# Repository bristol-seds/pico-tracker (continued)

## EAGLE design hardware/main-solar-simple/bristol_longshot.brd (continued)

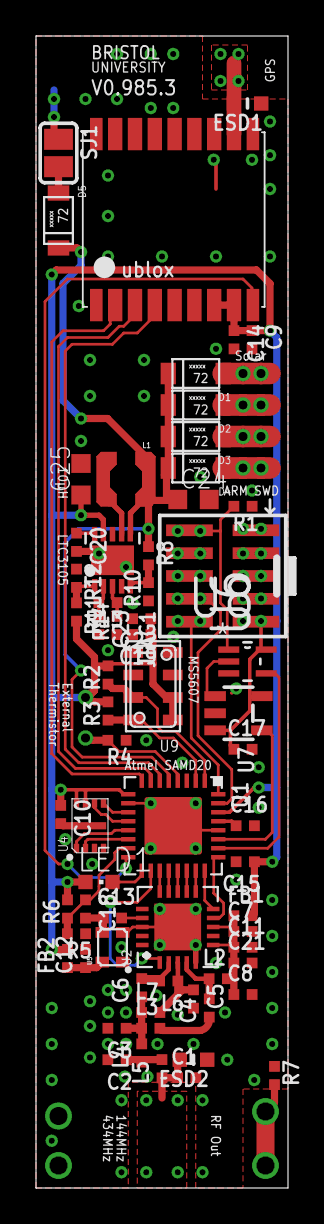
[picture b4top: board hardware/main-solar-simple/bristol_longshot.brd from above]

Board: 2 copper layers, 14.0 x 64.0 mm, 66 parts (0 on the bottom side), 50 nets.

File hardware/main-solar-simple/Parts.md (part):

# Parts List

** Parts for HF Section not yet included **

----
### Active

| Part | Description | Supplier | Quantity Required | Notes
| ---  | ---         | ---       | ---               | ---
|ATSAMD20E17A-MU|ATMEL - MCU, 32BIT, CORTEX-M0+, 48MHZ, QFN-32|[2361006](http://uk.farnell.com/webapp/wcs/stores/servlet/Search?st=2361006) [556-ATSAMD20E17A-MU](http://uk.mouser.com/Search/Refine.aspx?N=1323043&Keyword=55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|1|U1
|SI4468-A2A-IM|SILICON LABS - RF TRANSCEIVER, 0.142-1.05GHZ, HQFN-20|[2462639](http://uk.farnell.com/webapp/wcs/stores/servlet/Search?st=2462639) [634-SI4468-A2A-IM](http://uk.mouser.com/Search/Refine.aspx?N=1323043&Keyword=63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|1|U2
| UBLOX MAX-8C | GPS | [HAB Supplies](http://ava.upuaut.net/store/index.php?route=product/product&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 | 1 | U3
|SST25WF040BT-40I/NP|MICROCHIP - FLASH, 4MBIT, 40MHZ, USON-8|[2414758](http://uk.farnell.com/webapp/wcs/stores/servlet/Search?st=2414758) [579-25WF040BT-40I/NP](http://uk.mouser.com/Search/Refine.aspx?N=1323043&Keyword=57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|1|U4 memory 4Mbit
|X1G0041310008 TG-5006CJ-17H 16.369MHZ|EPSON - CRYSTAL, TCXO, TG-5006CJ-17H, 16.369 MHZ|[2405790](http://uk.farnell.com/webapp/wcs/stores/servlet/Search?st=2405790)|1|U5 TCXO Si4xxx
|LTC3105EDD#PBF|LINEAR TECHNOLOGY - BOOST, 400MA, MPPC, 10DFN|[1898600](http://uk.farnell.com/webapp/wcs/stores/servlet/Search?st=1898600)|1|U6 Solar Energy Boost Converter
|TPS3123J18DBVT|TEXAS INSTRUMENTS - IC, 1.62V SUPPLY MONITOR SOT-23-5|[1755607](http://uk.farnell.com/webapp/wcs/stores/servlet/Search?st=1755607) [595-TPS3123J18DBVT](http://uk.mouser.com/Search/Refine.aspx?N=1323043&Keyword=59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|1|U7 watchdog
|SN74LVC1G32DCKR|TEXAS INSTRUMENTS - IC, SINGLE 2 INPUT OR GATE, SMD|[1470880](http://uk.farnell.com/webapp/wcs/stores/servlet/Search?st=1470880) [595-SN74LVC1G32DCKR](http://uk.mouser.com/Search/Refine.aspx?N=1323043&Keyword=59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|1|U8 or-gate, watchdog subsystem
|MS560702BA03-50|MEASUREMENT SPECIALTIES - Pressure Sensor, QFN, 8, -40 Â°C, 85 Â°C, 1.8 V, 3.6 V|[2362660](http://uk.farnell.com/webapp/wcs/stores/servlet/Search?st=2362660)|1|U9 MS5607 Pressure / Temperature sensor
|RB161M-20TR|ROHM - Small Signal Schottky Diode, Single, 25 V, 1 A, 350 mV, 30 A, 125 Â°C|[1525484](http://uk.farnell.com/webapp/wcs/stores/servlet/Search?st=1525484)|5|D1, D2, D3, D4, D5 Small signal schotty diode
----

### Passives

| Part | Description | Supplier | Quantity Required | Notes
| ---  | ---         | ---       | ---               | ---
|LPS3015-103MRB|COILCRAFT - Surface Mount Power Inductor, AEC-Q200 LPS3015 Series, 10 ÂµH, Â± 20%, Shielded, 0.44 ohm, 550 mA|[2408024](http://uk.farnell.com/webapp/wcs/stores/servlet/Search?st=2408024)|1|L11 10µH LPS3015
|0402AF-221XJLU|COILCRAFT - Surface Mount High Frequency Inductor, 0402AF Series, 220 nH, Â± 5%, 0402 [1005 Metric], 1.15 GHz|[2285640](http://uk.farnell.com/webapp/wcs/stores/servlet/Search?st=2285640)|1|L2 220nH radio
|LQG15HN56NJ02D|MURATA - INDUCTOR, 0402 CASE, 56NHÂ±5%|[1343091](http://uk.farnell.com/webapp/wcs/stores/servlet/Search?st=1343091)|1|L3 56nH rf filter
|L-07C18NJV6T|JOHANSON TECHNOLOGY - Surface Mount High Frequency Inductor, L-07C Series, 18 nH, Â± 5%, 0402 [1005 Metric], 0.65 ohm|[1865775](http://uk.farnell.com/webapp/wcs/stores/servlet/Search?st=1865775)|1|L4, L5 18nH rf filter
| L6, L7 | DNP ||| si4xxx rx
|MC00625W0402110K|MULTICOMP - Surface Mount Chip Resistor, Thick Film, MC Series, 10 kohm, 62.5 mW, Â± 1%, 50 V|[1358069](http://uk.farnell.com/webapp/wcs/stores/servlet/Search?st=1358069)|7|R1, R2, R3 10k
|ERA2AED104X|PANASONIC ELECTRONIC COMPONENTS - Surface Mount Chip Resistor, Metal Film, AEC-Q200 ERA Series, 100 kohm, 63 mW, Â± 0.5%, 25 V|[2324718](http://uk.farnell.com/webapp/wcs/stores/servlet/Search?st=2324718)|1|R4 100k precise
|CRG0402F100K|TE CONNECTIVITY - Surface Mount Chip Resistor, Thick Film, CRG Series, 100 kohm, 63 mW, Â± 1%, 50 V|[2331442](http://uk.farnell.com/webapp/wcs/stores/servlet/Search?st=2331442)|2|R5, R6 100k
|RC0402JR-070RL|YAGEO (PHYCOMP) - Surface Mount Chip Resistor, Thick Film, RC Series, 0 ohm, 62.5 mW, Â± 5%, 50 V, 0402 [1005 Metric]|[9232516](http://uk.farnell.com/webapp/wcs/stores/servlet/Search?st=9232516)|1|R7 Bridge 0Ω
| R8 | DNP ||| connect MPPT set when battery only is used
|CRG0402F82K|TE CONNECTIVITY - Surface Mount Chip Resistor, Thick Film, CRG Series, 82 kohm, 63 mW, Â± 1%, 50 V, 0402 [1005 Metric]|[2331569](http://uk.farnell.com/webapp/wcs/stores/servlet/Search?st=2331569)|3|R10, R12, R14 LTC3105 82k
|CRG0402F68K|TE CONNECTIVITY - Surface Mount Chip Resistor, Thick Film, CRG Series, 68 kohm, 63 mW, Â± 1%, 50 V, 0402 [1005 Metric]|[2331557](http://uk.farnell.com/webapp/wcs/stores/servlet/Search?st=2331557)|1|R11 LTC3105 FB 68k
|MC00625W0402156K|MULTICOMP - Surface Mount Chip Resistor, Thick Film, MC Series, 56 kohm, 62.5 mW, Â± 1%, 50 V|[1358089](http://uk.farnell.com/webapp/wcs/stores/servlet/Search?st=1358089)|1|R13 LTC3105 LDOFB 56k
|GRM1555C1H8R2CA01D|MURATA - SMD Multilayer Ceramic Capacitor, GRM Series, 8.2 pF, Â± 0.25pF, C0G / NP0, 50 V, 0402 [1005 Metric]|[1828874](http://uk.farnell.com/webapp/wcs/stores/servlet/Search?st=1828874)|2|C1, C3 8.2pF
|MC0402N150J500CT|MULTICOMP - SMD Multilayer Ceramic Capacitor, MC Series, 15 pF, Â± 5%, C0G / NP0, 50 V, 0402 [1005 Metric]|[1758945](http://uk.farnell.com/webapp/wcs/stores/servlet/Search?st=1758945)|3|C2, C4, C7 15pF
| C5, C6 | DNP ||| si4xxx rx
|MC0402N101J500CT|MULTICOMP - SMD Multilayer Ceramic Capacitor, MC Series, 100 pF, Â± 5%, C0G / NP0, 50 V, 0402 [1005 Metric]|[1758969](http://uk.farnell.com/webapp/wcs/stores/servlet/Search?st=1758969)|3|C8, C9, C10 100pF
|MC0402X104K100CT|MULTICOMP - SMD Multilayer Ceramic Capacitor, MC Series, 0.1 ÂµF, Â± 10%, X5R, 10 V, 0402 [1005 Metric]|[1759380](http://uk.farnell.com/webapp/wcs/stores/servlet/Search?st=1759380)|9|C11, C12, C13, C14, C15, C16, C17, C18, C19 100nF
|GRM155R61E105KA12D|MURATA - SMD Multilayer Ceramic Capacitor, GRM Series, 1 ÂµF, Â± 10%, X5R, 25 V, 0402 [1005 Metric]|[2218855](http://uk.farnell.com/webapp/wcs/stores/servlet/Search?st=2218855)|1|C20 LTC3015 AUX 1µF
|GRM155R60J225ME15D|MURATA - SMD Multilayer Ceramic Capacitor, GRM Series, 2.2 ÂµF, Â± 20%, X5R, 6.3 V, 0402 [1005 Metric]|[2362088](http://uk.farnell.com/webapp/wcs/stores/servlet/Search?st=2362088)|1|C21 Radio Bypass 2.2µF
|C1005X5R0J475M050BC|TDK - SMD Multilayer Ceramic Capacitor, C Series, 4.7 ÂµF, Â± 20%, X5R, 6.3 V, 0402 [1005 Metric]|[2309027](http://uk.farnell.com/webapp/wcs/stores/servlet/Search?st=2309027)|2|C22, C23 MS5607 Bypass, LTC3105 LDO 4.7µF
|06036D106MAT2A|AVX - SMD Multilayer Ceramic Capacitor, 10 ÂµF, Â± 20%, X5R, 6.3 V, 0603 [1608 Metric]|[1833804](http://uk.farnell.com/webapp/wcs/stores/servlet/Search?st=1833804)|2|C24, C25 LTC3105 in, out 10µF 0603

----

### Misc

| Part | Description | Supplier | Quantity Required | Notes
| ---  | ---         | ---       | ---               | ---
|20021121-00010C4LF.|FCI - Board-To-Board Connector, Minitek127 20021121 Series, Surface Mount, Header, 10, 1.27 mm|[1865279](http://uk.farnell.com/webapp/wcs/stores/servlet/Search?st=1865279) [649-202112100010C4LF](http://uk.mouser.com/Search/Refine.aspx?N=1323043&Keyword=64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|1|JTAG1
|742792731|WURTH ELEKTRONIK - FERRITE BEAD, 0.09OHM, 1.2A, 0402|[1961698](http://uk.farnell.com/webapp/wcs/stores/servlet/Search?st=1961698)|2|FB1, FB2
|CG0603MLC-05LE|BOURNS - ESD Protection Device, 25 V, 5 V, 0603, 2|[1828732](http://uk.farnell.com/webapp/wcs/stores/servlet/Search?st=1828732)|0|ESD1, ESD2
|B57861S0103F040|EPCOS - THERMISTOR, 10K, 1%, NTC, RAD|[679446](http://uk.farnell.com/webapp/wcs/stores/servlet/Search?st=679446)|1|External Thermistor
| | Antenna Wire | [ebay](http://www.ebay.co.uk/itm/Ernie-Ball-Custom-Gauge-Guitar-Sin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 ) | 1 | Ernie Ball .013
| | Energizer Ultimate Lithium AAA | [datasheet](http://data.energizer.com/PDFs/l92.pdf) | 1 | ~1200mAh

----

## AAA Hardware

| ID | Part Number | Description | Supplier | Order Code | Quantity
| --- | --- | --- | --- | --- | ---
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
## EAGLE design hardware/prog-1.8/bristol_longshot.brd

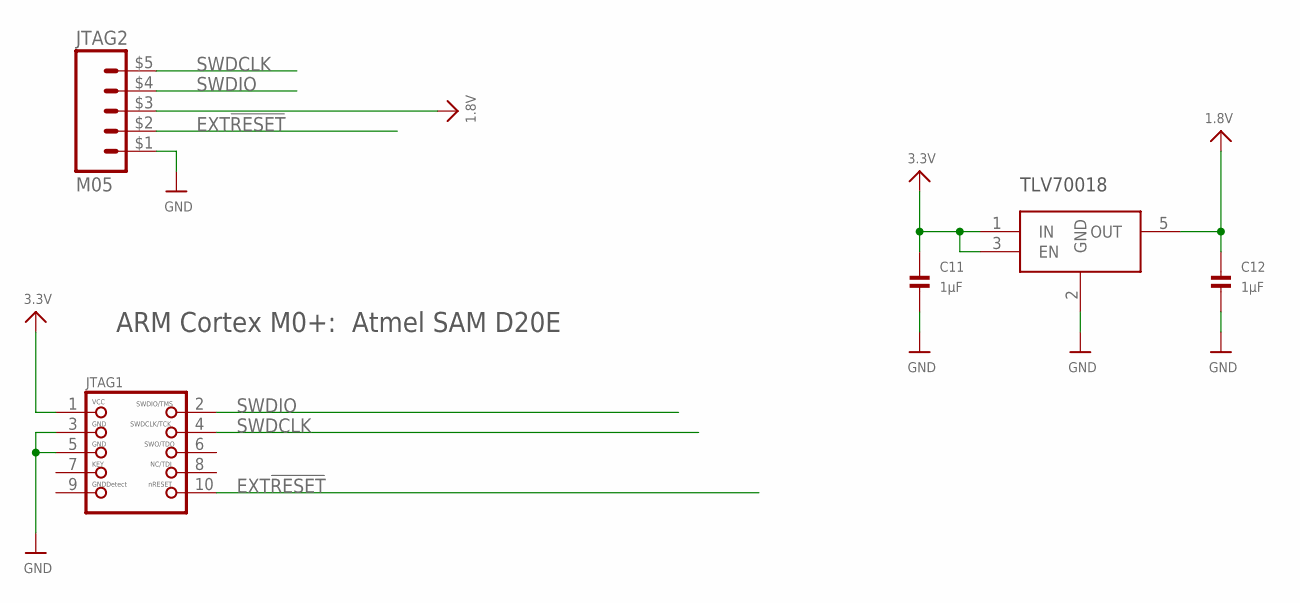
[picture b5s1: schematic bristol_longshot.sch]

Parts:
C11, C12: 1µF; _0402
JTAG1: JTAG-CORTEXM3SMT; 2X05_1.27MM_SMT
JTAG2: M05; M05_SIDE
U1: TLV70018DCK; SC70-5L

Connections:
1.8V: C12.1, JTAG2.$3 (3), U1.5 (OUT)
3.3V: C11.1, JTAG1.1, U1.1 (IN), U1.3 (EN)
EXT!RESET: JTAG1.10, JTAG2.$2 (2)
GND: C11.2, C12.2, JTAG1.3, JTAG1.5, JTAG2.$1 (1), U1.2 (GND)
SWDCLK: JTAG1.4, JTAG2.$5 (5)
SWDIO: JTAG1.2, JTAG2.$4 (4)

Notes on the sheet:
ARM Cortex M0+: Atmel SAM D20E
TLV70018

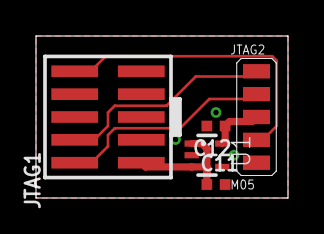
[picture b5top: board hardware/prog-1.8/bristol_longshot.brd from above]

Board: 2 copper layers, 14.0 x 9.0 mm, 5 parts (0 on the bottom side), 6 nets.

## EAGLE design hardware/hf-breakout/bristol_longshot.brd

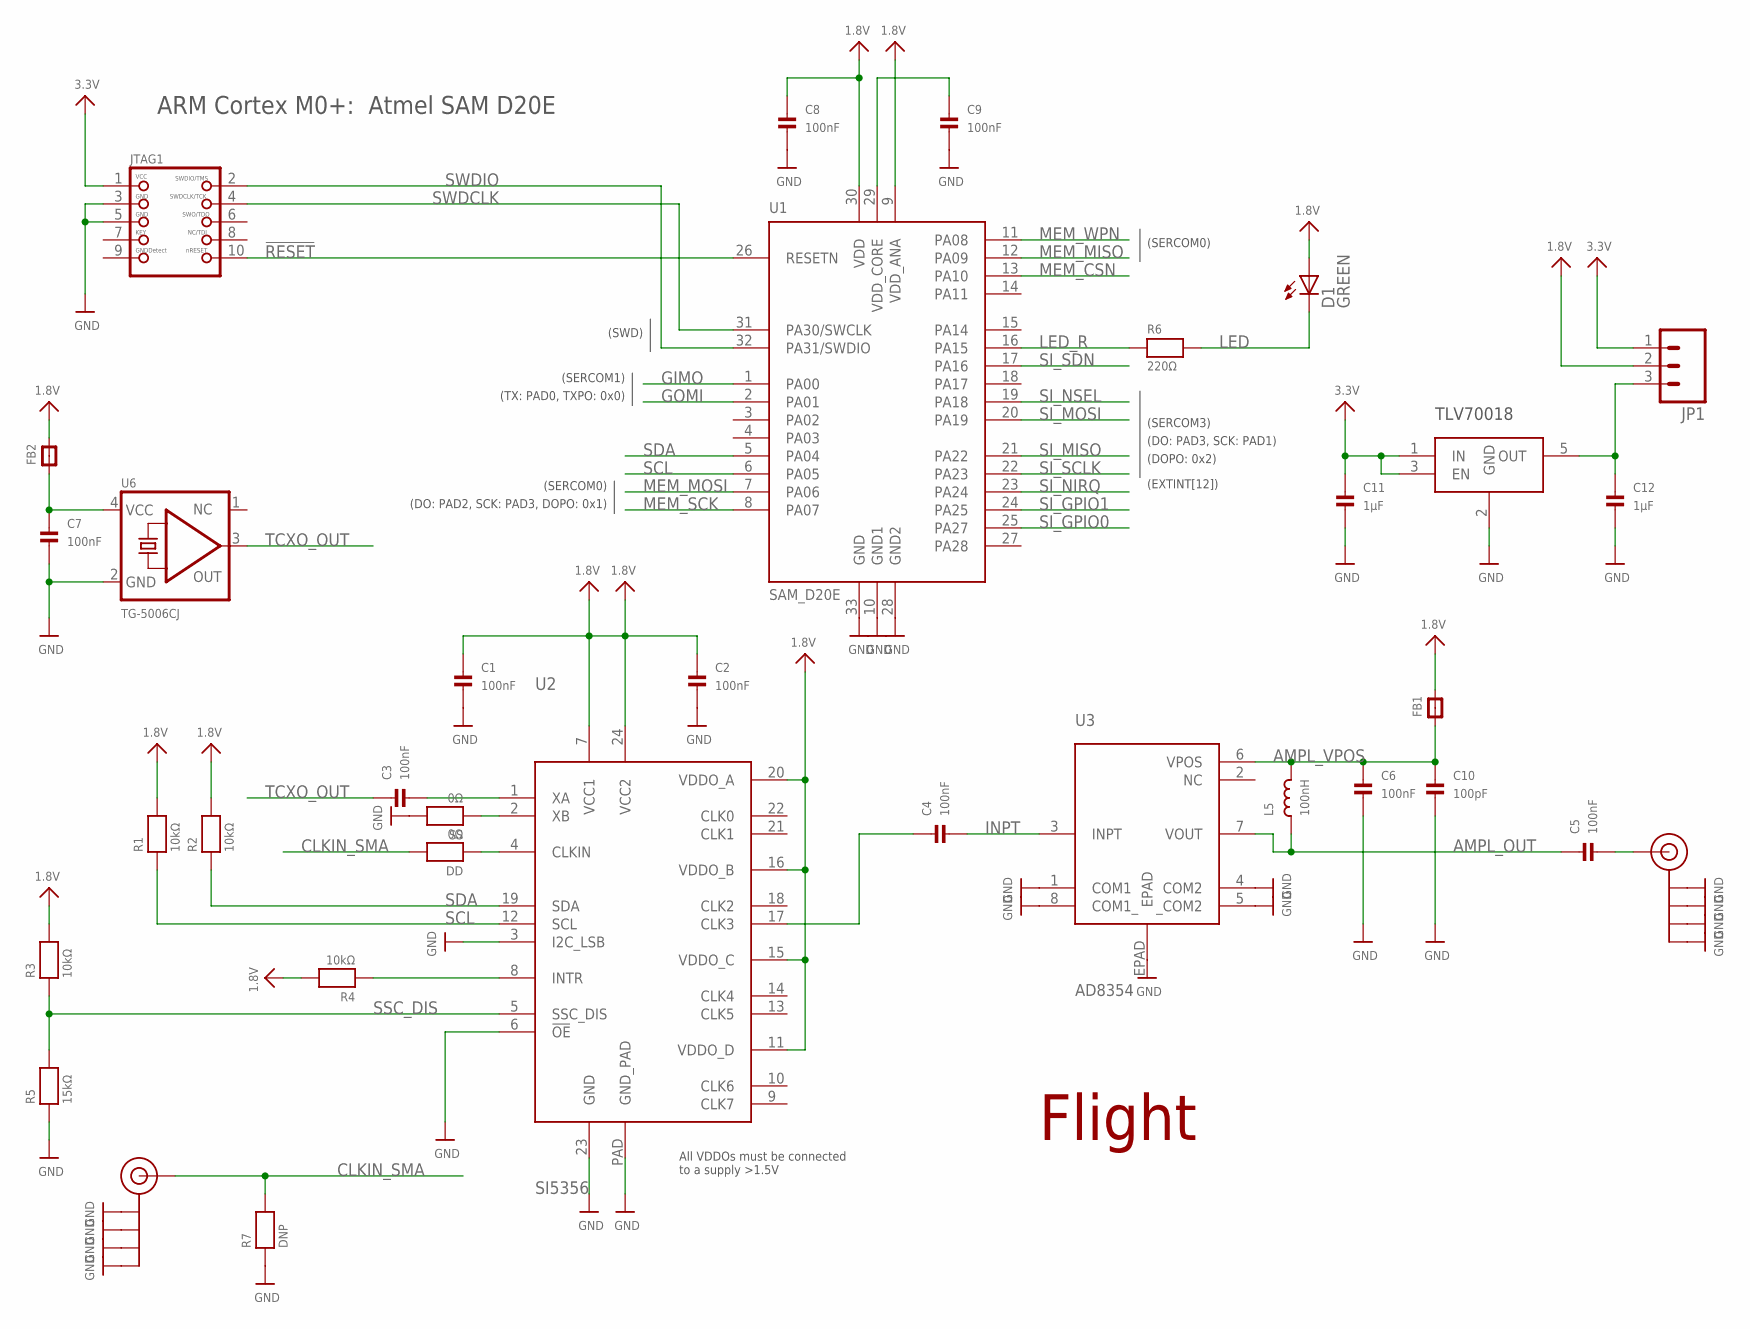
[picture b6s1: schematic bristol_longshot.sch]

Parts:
C1, C2, C3, C4, C5, C6, C7, C8, C9: 100nF; _0402
C10: 100pF; _0402
C11, C12: 1µF; _0402
D1: GREEN; CHIPLED_0603
DD: 0Ω; _0402
FB1, FB2: FERRITE_0402; _0402
IC3: TLV70018DCK; SC70-5L
J$1, J$2: SMA_EDGE; SMA-EDGE
JP1: M03LOCK; 1X03_LOCK
JTAG1: JTAG-CORTEXM3SMT; 2X05_1.27MM_SMT
L5: 100nH; _0402
R1, R2, R3, R4: 10kΩ; _0402
R5: 15kΩ; _0402
R6: 220Ω; _0402
R7: DNP; _0402
SS: 0Ω; _0402
U1: SAM_D20E; QFN32_5MM
U2: SI5356; QFN24_4MM
U3: AD8354; LFCSP_VD_8
U6: TG-5006CJ; TC-5006CJ

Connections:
1.8V: C1.1, C2.1, C8.1, D1.A, FB1.2, FB2.2, JP1.2, R1.2, R2.2, R3.2, R4.2, U1.9 (VDD_ANA), U1.30 (VDD), U2.7 (VCC1), U2.11 (VDDO_D), U2.15 (VDDO_C), U2.16 (VDDO_B), U2.20 (VDDO_A), U2.24 (VCC2)
3.3V: C11.1, IC3.1 (IN), IC3.3 (EN), JP1.1, JTAG1.1; also elsewhere on the board
!RESET: JTAG1.10, U1.26 (RESETN)
AMPL_OUT: C5.1, L5.1, U3.7 (VOUT)
AMPL_VPOS: C6.1, C10.1, FB1.1, L5.2, U3.6 (VPOS)
CLKIN: DD.1, U2.4 (CLKIN)
CLKIN_SMA: DD.2, J$1.SIG (SIGNAL), R7.2
GIMO: U1.1 (PA00)
GND: C1.2, C2.2, C6.2, C7.2, C8.2, C9.2, C10.2, C11.2, C12.2, IC3.2 (GND), J$1.GND@0 (GND), J$1.GND@1 (GND), J$1.GND@2 (GND), J$1.GND@3 (GND), J$2.GND@0 (GND), J$2.GND@1 (GND), J$2.GND@2 (GND), J$2.GND@3 (GND), JTAG1.3, JTAG1.5, R5.1, R7.1, SS.2, U1.10 (GND1), U1.28 (GND2), U1.33 (GND), U2.3 (I2C_LSB), U2.6 (!OE), U2.23 (GND), U2.PAD (GND_PAD), U3.1 (COM1), U3.4 (COM2), U3.5 (_COM2), U3.8 (COM1_), U3.EPAD, U6.2 (GND); also elsewhere on the board
GOMI: U1.2 (PA01)
HF: C5.2, J$2.SIG (SIGNAL)
HF_CLK: C4.1, U2.17 (CLK3)
INPT: C4.2, U3.3 (INPT)
INTR: R4.1, U2.8 (INTR)
LED: D1.C, R6.2
LED_R: R6.1, U1.16 (PA15)
MEM_CSN: U1.13 (PA10)
MEM_MISO: U1.12 (PA09)
MEM_MOSI: U1.7 (PA06)
MEM_SCK: U1.8 (PA07)
MEM_WPN: U1.11 (PA08)
unnamed 22: C12.1, IC3.5 (OUT), JP1.3; also elsewhere on the board
SCL: R1.1, U1.6 (PA05), U2.12 (SCL)
SDA: R2.1, U1.5 (PA04), U2.19 (SDA)
SI_GPIO0: U1.25 (PA27)
SI_GPIO1: U1.24 (PA25)
SI_MISO: U1.21 (PA22)
SI_MOSI: U1.20 (PA19)
SI_NIRQ: U1.23 (PA24)
SI_NSEL: U1.19 (PA18)
SI_SCLK: U1.22 (PA23)
SI_SDN: U1.17 (PA16)
SSC_DIS: R3.1, R5.2, U2.5 (SSC_DIS)
SWDCLK: JTAG1.4, U1.31 (PA30/SWCLK)
SWDIO: JTAG1.2, U1.32 (PA31/SWDIO)
TCXO_OUT: C3.1, U6.3 (OUT)
TCXO_VDD: C7.1, FB2.1, U6.4 (VCC)
VDD_CORE: C9.1, U1.29 (VDD_CORE)
XA: C3.2, U2.1 (XA)
XB: SS.1, U2.2 (XB)

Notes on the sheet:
ARM Cortex M0+: Atmel SAM D20E
(SERCOM3)
(SWD)
(SERCOM0)
(EXTINT[12])
(DO: PAD3, SCK: PAD1)
(DOPO: 0x2)
(DO: PAD2, SCK: PAD3, DOPO: 0x1)
(SERCOM1)
(TX: PAD0, TXPO: 0x0)
Flight
All VDDOs must be connected to a supply >1.5V
TLV70018

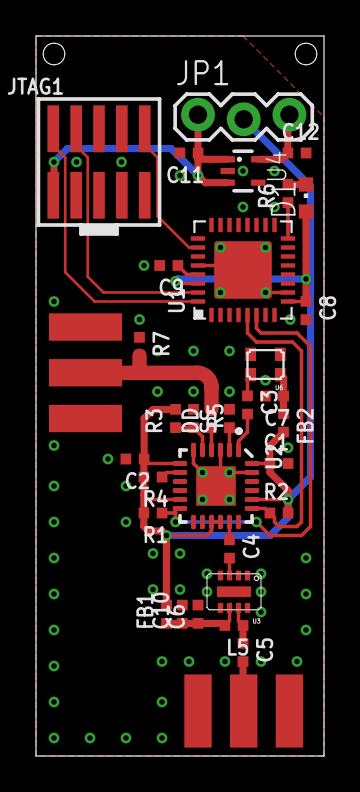
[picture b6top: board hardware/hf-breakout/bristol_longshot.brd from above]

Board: 2 copper layers, 16.0 x 40.0 mm, 34 parts (0 on the bottom side), 25 nets.

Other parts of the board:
U4: TLV70018DCK; SC70-5L

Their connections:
3.3V: U4.1, U4.3; also elsewhere on the board
GND: U4.2; also elsewhere on the board
unnamed 22: U4.5; also elsewhere on the board

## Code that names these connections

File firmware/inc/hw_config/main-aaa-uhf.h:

/*
 * Hardware definitions and configuations
 * Copyright (C) 2014  Richard Meadows <richardeoin>
 *
 * Permission is hereby granted, free of charge, to any person obtaining
 * a copy of this software and associated documentation files (the
 * "Software"), to deal in the Software without restriction, including
 * without limitation the rights to use, copy, modify, merge, publish,
 * distribute, sublicense, and/or sell copies of the Software, and to
 * permit persons to whom the Software is furnished to do so, subject to
 * the following conditions:
 *
 * The above copyright notice and this permission notice shall be
 * included in all copies or substantial portions of the Software.
 *
 * THE SOFTWARE IS PROVIDED "AS IS", WITHOUT WARRANTY OF ANY KIND,
 * EXPRESS OR IMPLIED, INCLUDING BUT NOT LIMITED TO THE WARRANTIES OF
 * MERCHANTABILITY, FITNESS FOR A PARTICULAR PURPOSE AND
 * NONINFRINGEMENT. IN NO EVENT SHALL THE AUTHORS OR COPYRIGHT HOLDERS BE
 * LIABLE FOR ANY CLAIM, DAMAGES OR OTHER LIABILITY, WHETHER IN AN ACTION
 * OF CONTRACT, TORT OR OTHERWISE, ARISING FROM, OUT OF OR IN CONNECTION
 * WITH THE SOFTWARE OR THE USE OR OTHER DEALINGS IN THE SOFTWARE.
 */

#ifndef HW_CONFIG_H
#define HW_CONFIG_H

#include "port.h"
#include "samd20.h"
#include "adc/adc.h"

/*
 * Convenience definitions for available GPIO modules
 */
#if (PORT_GROUPS > 0)
#define PORTA		PORT->Group[0]
#endif
#if (PORT_GROUPS > 1)
#define PORTB		PORT->Group[1]
#endif
#if (PORT_GROUPS > 2)
#define PORTC		PORT->Group[2]
#endif
#if (PORT_GROUPS > 3)
#define PORTD		PORT->Group[3]
#endif


//#define XPLAINED

/**
 * LED
 */
#ifdef XPLAINED
#define LED0_PIN		PIN_PA14
#else
#define LED0_PIN		PIN_PA16
#endif

/**
 * GPS
 */
#define GPS_SERCOM		(SercomUsart*)SERCOM0
#define GPS_SERCOM_MOGI_PIN	PIN_PA06
#define GPS_SERCOM_MOGI_PINMUX	PINMUX_PA06D_SERCOM0_PAD2
#define GPS_SERCOM_MIGO_PIN	PIN_PA07
#define GPS_SERCOM_MIGO_PINMUX	PINMUX_PA07D_SERCOM0_PAD3
#define GPS_SERCOM_MUX		USART_RX_3_TX_2_XCK_3
#define GPS_GCLK		GCLK_GENERATOR_1

#define GPS_TYPE_UBX
#define GPS_BAUD_RATE		9600
#define GPS_PLATFORM_MODEL	UBX_PLATFORM_MODEL_AIRBORNE_1G
#define GPS_TIMEPULSE_PIN	PIN_PA05
#define GPS_TIMEPULSE_PINMUX	PINMUX_PA05A_EIC_EXTINT5
#define GPS_TIMEPULSE_FREQ      1
#define GPS_TIMEPULSE_EXTINT	5
#define GPS_RESET_PIN		PIN_PA15

#define GPS_FLIGHT_STATE_THREASHOLD_M	8000 /* 8km altitude */

/**
 * USART Loopback Testing
 */
#define USART_MUX_LOOPBACK	USART_RX_2_TX_2_XCK_3


/**
 * Battery ADC
 */
#define BATTERY_ADC			1
#define BATTERY_ADC_PIN		PIN_PA03
#define BATTERY_ADC_PINMUX	PINMUX_PA03B_ADC_AIN1
#define BATTERY_ADC_CHANNEL	ADC_POSITIVE_INPUT_PIN1
#define BATTERY_ADC_CHANNEL_DIV	0.3125 /* ??? */
#define BATTERY_ADC_REFERENCE	ADC_REFERENCE_INT1V

/**
 * External Thermistor ADC
 */
#define THERMISTOR_ADC		0
#define THERMISTOR_ADC_PIN	PIN_PA03
#define THERMISTOR_ADC_PINMUX	PINMUX_PA03
#define THERMISTOR_ADC_CHANNEL	ADC_POSITIVE_INPUT_PIN1
#define THERMISTOR_ADC_CHANNEL_DIV 1
#define THERMISTOR_ADC_REFERENCE ADC_REFERENCE_INTVCC0 /* internal 1/1.48 VCC reference */

/**
 * Solar ADC
 */
#define SOLAR_ADC			0
#define SOLAR_ADC_PIN		PIN_PA04
#define SOLAR_ADC_PINMUX	PINMUX_PA04B_ADC_AIN4
#define SOLAR_ADC_CHANNEL	ADC_POSITIVE_INPUT_PIN4
#define SOLAR_ADC_CHANNEL_DIV	1
#define SOLAR_ADC_REFERENCE	ADC_REFERENCE_INT1V

/**
 * Battery
 */
#define RECHARGABLE_BATTERY	0

/**
 * Cycle Times
 */
#define CYCLE_TIME_FAST		(30)   /* always 30 seconds */
#define CYCLE_TIME_SLOW		(30)

/**
 * Radio
 */
#define SI4xxx_RADIO_PN		0x4467
#define SI4xxx_SERCOM		(SercomSpi*)SERCOM3
#define SI4xxx_SERCOM_MOSI_PIN	PIN_PA19
#define SI4xxx_SERCOM_MOSI_PINMUX PINMUX_PA19D_SERCOM3_PAD3
#define SI4xxx_SERCOM_MISO_PIN	PIN_PA22
#define SI4xxx_SERCOM_MISO_PINMUX PINMUX_PA22C_SERCOM3_PAD0
#define SI4xxx_SERCOM_SCK_PIN	PIN_PA23
#define SI4xxx_SERCOM_SCK_PINMUX	PINMUX_PA23C_SERCOM3_PAD1
#define SI4xxx_SERCOM_MUX	SPI_SIGNAL_MUX_SETTING_M
#define SI4xxx_SEL_PIN		PIN_PA18
#define SI4xxx_IRQ_PIN		PIN_PA24
#define SI4xxx_IRQ_PINMUX	PINMUX_PA24A_EIC_EXTINT12
#define SI4xxx_SDN_PIN		PIN_PA17
#define SI4xxx_GPIO0_PIN	PIN_PA27
#define SI4xxx_GPIO1_PIN	PIN_PA25
#define SI4xxx_GPIO1_PINMUX	PINMUX_PA25F_TC5_WO1
#define SI4xxx_TCXO_FREQUENCY	16369000

/**
 * RF Power @ 1.8V
 *
 * These values are taken from the datasheet, but the
 * difference between them has been measured as 6dB
 */
#define RF_POWER_14dBm		0x7f
#define RF_POWER_8dBm		0x7f /* tested in lab (36) */


/**
 * RF Enable
 *
 * Disable this when there's no antenna connected
 */
#define RF_TX_ENABLE		1

/**
 * LF Clock
 */
#define USE_LFTIMER			0

/**
 * XOSC
 */
#define USE_XOSC				1
#define XOSC_FREQUENCY			16369000
#define XOSC_GCLK_DIVIDE		2         /* ~8MHz on GCLK */
#define OSC8M_GCLK_DIVIDE		1         /* ~8MHz on GCLK */
#define MEASURE_XOSC			1

/**
 * Telemetry
 */
#define TELEMETRY_ENABLE		1
#define TELEMETRY_USE_GEOFENCE	0
#define TELEMETRY_FREQUENCY		434612500
#define TELEMETRY_POWER			RF_POWER_8dBm

/**
 * APRS
 */
#define APRS_ENABLE			0
#define APRS_USE_GEOFENCE	0
#define APRS_POWER			RF_POWER_14dBm

/**
 * Backlog
 */
#define BACKLOG_RECORD_BACKLOG	0

/**
 * Watchdog Timer
 *
 * There is a performance penalty to using the watchdog - you must
 * wait up to 1/16kHz when kicking to sync with it. Disable when not in use
 */
//#define DEBUG_USE_INTWATCHDOG	0
#define WDT_GCLK		GCLK_GENERATOR_4

/**
 * External Watchdog Timer
 */
#define WDT_WDI_PIN		PIN_PA28

/**
 * SWD
 */
#define SWD_SWDCLK_PIN		PIN_PA30
#define SWD_SWDCLK_PINMUX	PINMUX_PA30G_CORE_SWCLK
#define SWD_SWDIO_PIN		PIN_PA31


/**
 * Interrupt Priority
 */
#define WDT_INT_PRIO		0 /* Early warning interrupt */

#define TC0_INT_PRIO		1 /* Telemetry Tick Timer */

#define GPS_SERCOM_INT_PRIO	2 /* GPS USART Rx */

#define EIC_INT_PRIO		3 /* Timepulse, telemetry */

#define TC2_INT_PRIO		3 /* XOSC Measure Timer */

#define TC4_INT_PRIO		3 /* LF timer */
#define RTC_INT_PRIO		3 /* RTC */

#define ADC_INT_PRIO		3 /* ADC */

#endif /* HW_CONFIG_H */

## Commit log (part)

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2015-07-24 Timeout and retries on gps position and time. Lock and wait for hardware reset after 5 tries
2015-07-24 [Ooops] Fix logical error from eaa6469
2015-07-24 Enabled aprs parameters for flight
2015-07-25 Invalidate bad backlog items as they're read from memory
2015-07-25 Link to parts list for ubseds6 tag
2015-07-25 UBSEDS9 pre-flight
2015-08-01 raw_parser: Prompt if filename not specified
2015-08-01 Added habitat upload. Not complete yet but close #6
2015-08-02 Habitat upload done. 'time_created' corresponds to the backlog time, gets sorted correctly by the habitat couchdb views
2015-08-02 Added barometeric altitude model and testcase
2015-09-13 Updated main tracker solar design to use a LTC3105 energy harvester for solar and a 3V primary lithium for backup. Work in Progress
2015-09-15 Updated schematic labels, fixed R11 value
2015-09-15 Added README describing hardware revisions
2015-09-21 Hardware V0.985.2, replaces BMP180 with MS5607
2015-09-22 Small board change..
2015-10-01 Added module and tests for BMP180
2015-10-01 Add option for TELEMETRY_USE_GEOFENCE, disable APRS
2015-10-06 Tidy various compiler warnings
2015-10-06 Save some flash
2015-10-06 Enable aprs, telemetry geofence for testing
2015-10-06 Add thermistor voltage readings to analogue.c
    analogue.c is now configured from hw_config.h. Refactored a few things including the testcase.
2015-10-06 Added data field to UKHAS string
2015-10-08 Hardware v0.985.3, reduce external thermistor holes to 0.5mm dia
2015-10-08 Fix GPS reset
2015-10-08 Change data collection to once per minute, aligned with the Telemetry top-of-minute.
    Also some more rigourous accounting of the ukhas telemetry size
2015-10-09 Add BMP180 to data.c, format output correctly
2015-10-09 Finish removing semihost stuff
2015-10-10 Memory JEDEC ID in variable for debugging
2015-10-10 Increase ADC sample length, use internal ADC averaging.
2015-10-11 UBSEDS10
2015-10-18 Added UBX CFG PWR frame to GPS. Useful for putting GPS in "shutdown"
2015-10-28 Added hardware note for UBSEDS10-11
2015-10-28 [low-power-side] More work on board, vaguely complete. Added parts list
2015-11-02 Re-organised for two barometers
2015-11-02 [low-power-side] Added 10k i2c pull ups
    v0.986.0 -> v0.986.1
2015-11-10 low-power-side v0.986.4. Added LIS2D accelerometer. Optional
2015-11-14 [geofence] Restructure geofence notebooks, split aprs into frequency zone and no_aprs areas
    location.c need to be refactored to reflect these changes
2015-11-16 [gps] Started support for SiRF IV gps units in gps_osp.c. Split this away from gps_ubx.c
    TODO: Integrate osp gps support into cron.c, data.c etc.
2015-11-17 [low-power-side] v0.986.5 Added TS3006 low power clock
2015-11-20 [bugfix] Always 8-bit write corrected generator ID before reading
2015-11-22 [low power] v0.986.7. Changed low power lf clock, added vreg on breakout for optional power testing
2015-11-22 Commit thermistor.c, should have been added in f35ccb540b734aa2510d3fa96e54fe8df9596a13
2015-11-22 Rename geofence_aprs to geofence_aprs_zones for clarity
2015-11-22 [bugfix] re-order lat and lon. This will be convention from now on
2015-11-30 [powersave] Keep memory in deep power down and interface disabled when not in use
    In total shaves 50 - 100µA off the shutdown state, reduces memory power to negligible again. Power saved from both interface (about 35µA) and from placing memory in shutdown (40µA maybe).
2015-12-01 [low-power] v0.986.8. Changed memory pads, GPS LDO and specified SAMD20E18A-MN with more flash and higher grade packaging
2015-12-13 Add support for faster contestia modes
2015-12-13 [pips] Support for n pips. For a single pip use n = 1
2015-12-13 Just disable this. Internal watchdogs suck
2015-12-13 low-power-breakout] Fix some bit-rot
2015-12-13 More verbose part number checking loop in si_trx
2015-12-19 [contestia] make preamble length constant despite number of tones
2015-12-19 [ubx] Add ubx-cfg-rst message on startup
2015-12-20 [osp] Clear the entirety of the packet
2015-12-20 Add rf transmit enable in hw config
2015-12-20 Various bit rot on parts lists
2015-12-21 [low-power] |v0.987.0|Low Power. Added 32kHz TCXO RC filters, replaced GPS LDO with MOSFET, remove IMU, vreg on b/out, update SE880 footprint, Watchdog, Radio, filter design
2015-12-22 [low-power] |v0.987.1|Low Power. Switch LF Clock to XOSC32K pin from GCLK_IO[0]. Allows feed to any GCLK. Bit-bang i2c instead
2015-12-24 Added i2c bit-banging. Broken, I can't be bothered to fix without a signal analyser
2015-12-31 Fix define do/while..
2016-01-14 Update telemetry rate for battery power.
    Once per minute below 8km, once every 4 minutes after that. Balloon unlikely to float
    below 8km unless something interesting is happening so this seems reasonable.
2016-01-14 [i2c-bb] Add timeout and error code return if slave fails to ack
2016-01-15 [radio] use si4461
    Have a working tested match for this
2016-01-15 [battery] Add 1.5V L91 battery voltage to uhf telemetry
2016-01-15 [gps-osp] ensure led is off during hibernate sequence
2016-01-15 [sequencer] Bodge to limit gps rate to once per 2 minutes
2016-01-16 [watchdog] Fix stupid in IDLE_WAIT_FOR_GPS from 73281c2
2016-01-16 Add testcase to pre-flight checklist
2016-01-16 [ms5607] Differentiate between ms5607 and ms5611 in hw_config.
2016-01-16 Reduce lat/long to 4 decimal places. This corresponds to 11m resolution at the equator which is plenty
2016-01-16 [thermistor] More 4ae5371
2016-01-18 [watchdog] Updated comments for ADM6823
2016-01-18 [ms5607] Attempt to initialise if this has previously failed
2016-01-19 [flight] UBSEDS13
2016-01-19 [pre-flight] correct mem_erase_all testcase name
2016-01-25 [backlog] Modularise raw_parser.py and create aprs_daemon.py to upload backlog data as it arrives
2016-02-01 point at the repo version (ubseds6) shown in the image, rather than the head which has changed a bit
    well it's almost the same version
2016-02-03 [geofence] Big overhaul of geofences to use an actual equal-area projection
    Use EASE world grid EPSG:3410 projection. Grid expansions/tolerances are now the same over the whole globe, less safety factor required.
    Also add US to UHF telemetry (carried from earlier removal of APRS in the US)
2016-02-05 [aprs.h] string functions handy
2016-02-05 [geofence-prefix] Added many more country prefixes
2016-02-10 [solar-breakout] Complete parts list
2016-02-22 [solar-breakout] add Q1 and Q2 to partslist
2016-02-28 [gps_osp] Added gps reset pin, using hacky resistor switch on the board
2016-02-28 [i2c][barometer] i2c is only used when barometer is active, fixes issue with PA01 being used by i2c
2016-02-29 [lftimer] Separate lf_timer_startup function, init GCLK2
2016-03-02 [gps_osp] Add gps_get_data wrapper, reinitialises GPS if required
2016-03-02 [cold-out] Implement cold-out functionality.
    Don't `gps_init` until the cold-out condition finishes.
2016-03-03 [si_trx] record frequency in si_frequency_configuration struct
2016-03-03 [gps] use wrapped function to re-init gps
2016-03-03 [sequencer,aprs] Allow APRS at the rate everything else happens
2016-03-03 [gps_osp] clear `OSP_PACKET_UPDATED` flags at the start of gps_setup
2016-03-04 [drift] Testing compensation of xosc drift against the lftimer. Doesn't work awfully well so disabled.
    The lftimer isn't stable enough, compensation would be possible over a longer timescale maybe.
2016-03-05 [gps_osp] set maximum number of reinits before we call in the watchdog
2016-03-05 [pre-flight] add note about cold out
2016-03-07 [aprs-daemon] add newline to rawdata output
2016-03-13 [aprs-daemon] update ukhas string for ubseds14
2016-03-14 [ukhas format] add flight-specific ukhas format, notes about updating format for new flights
2016-03-17 [Pre-flight] add notes about aprs-equations
2016-03-24 [geofence,tc] add seattle to tc
2016-03-26 [xosc] correct comment
2016-03-26 [low-power-solar] hw-config changes, add header guards for no timepulse or and no i2c operation
2016-03-27 [aprs-tools] re-organise aprs tools directory, start adding ubseds15 flight
2016-03-28 [lftimer->rtc] replace LF timer with always-running RTC timer
2016-03-28 [sequencer] update comment
2016-03-28 [gps_osp] fix compiler warnings - make it clear that osp_messages are volatile
2016-03-28 [lf-timer] Reduce xosc32k startup time to 100-200ms. Now there's no chance of hitting the wdt
2016-03-28 [aprs] try amplified path one-in-four times during the day when the battery is good
2016-03-28 [geofence_aprs_zones] Fix aprs zone for austrailia, add to test case
2016-03-29 [sequencer] pass the cycle time to the sequencer so the backlog rate can be kept constant at one-per-hour
2016-03-30 [low-power-solar] move markings to tStop layer
2016-04-02 [battery,bus] stay in cold out hibernate when the bus voltage is less than 2.5V
2016-04-10 [low-power-solar] finish of partslist
2016-04-14 [gps_osp] detect gps invalid if position (lat,long AND alt) remain _exactly_ the same between positions
2016-04-21 [tc,adc_battery_solar_read] fix and re-add this testcase
2016-04-21 [ubseds15] update stringify function
2016-04-24 [gps_osp] leave no-lock GPS running so that it can try to get a lock.
    Thought this was already the case but seemingly not
2016-04-24 [rf-tests] tidy
2016-04-26 [battery] move battery update to the end of the sequence
    If we don't have enough power to run *and* charge the battery then at least
    some charging will be done bfore a power reset
2016-04-27 [xosc] always _enable_ external tcxo when enabling hf clock
    XOSC_TCXO_SHUTDOWN_EN only control disabling
2016-04-29 [ubseds15] cold out to -70, allow gps to run for a day without reset, add deathwish
2016-05-07 [aprs,tools] specifiy exact callsigns in daemon filters to remove cruft
2016-06-02 [aprs-tools] bugfix for backlog for the 31st of the previous month
2016-07-01 [bugfix] fix days_in_month, add epoch calculation for se880 GPS
    Fixes bug with backlog write location, which lead to more recent data being overwritten
2016-07-16 [sequencer] change timings for continous transmission
    A minimum gap between APRS transmissions can be enforced
2016-07-16 [memory] use internal flash for backlog
2016-07-17 [pressure-temperature] only when baro in use
2016-07-17 [ariss[ only when arris in use
2016-07-17 [gps-ubx] update so it builds. TODO: test
2016-07-18 [ubseds16] set callsign, telemetry format
2016-07-29 [rtc] run at cycle time
2016-07-29 [ubseds16] set cycle time to always be 30 seconds
2016-07-30 [telemetry] reduce RAM usage, number of characters is limited by transmission time anyhow
2016-07-30 [flash] add checksum status to telemetry
2016-08-02 [solar-only] new hwconfig for solar only
2016-08-02 [geofence] reduce the prefix geofence to 20km resolution, cut out much of the southern hemisphere
2016-08-03 [geofence] prefix
2016-08-04 [gps_ubx] fixes for -O1
2016-08-04 [gps_ubx] wait at most 5 seconds for gps_ubx
2016-08-04 [ms5607] fix delay function
2016-08-04 [loader] add option for bootloader
2016-08-05 [memory] tidy
2016-08-05 [loader] initial fix of flash checking
2016-08-07 [aprs_daemon] be less selective with aprs-is filters
2016-08-12 [loader] add testcase for loader, but disable testcases from loader build
2016-08-12 add __NOPs to stop dodgy busy-wait loops being optimised out0
    Really need to get on top of these
2016-08-12 [flash status] transfer flash status from bootloader to application using random RAM location
2016-08-12 [ubseds17] start preparations for ubseds17, with ariss
2016-08-13 [thermistor_equation] fix testcase
2016-08-13 [pre-flight.md] changes to pre-flight instruction for callsign.h
2016-08-13 [battery] only wait half an hour before starting charging
2016-08-13 [Makefile] add loader command for programming loader
2016-08-13 [gps_osp] make ON_OFF signal longer
2016-08-13 [gps_osp] re-enable GPS re-inits, with a longer timeout period
2016-08-16 [gps_ubx] only output date if locked
